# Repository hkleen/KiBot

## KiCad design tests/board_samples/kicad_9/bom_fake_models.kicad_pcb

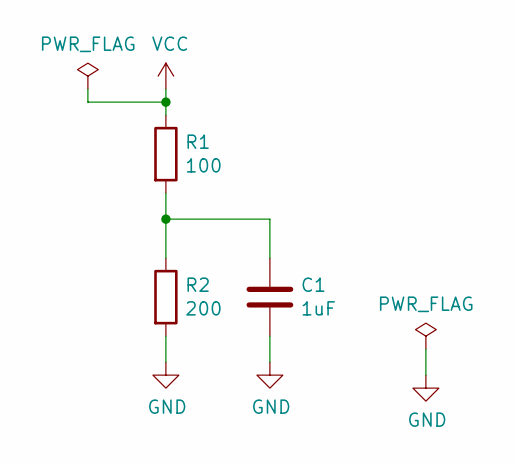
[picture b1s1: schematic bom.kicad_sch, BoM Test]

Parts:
C1: 1uF; C_0805_2012Metric
R1: 100; R_0805_2012Metric
R2: 200; R_0805_2012Metric

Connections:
GND: C1.2, R2.2
unnamed: C1.1, R1.2, R2.1
VCC: R1.1

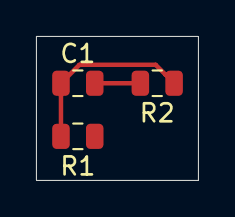
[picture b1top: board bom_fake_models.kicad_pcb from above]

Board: 2 copper layers, 9.0 x 8.0 mm, 3 parts (0 on the bottom side), 2 nets.

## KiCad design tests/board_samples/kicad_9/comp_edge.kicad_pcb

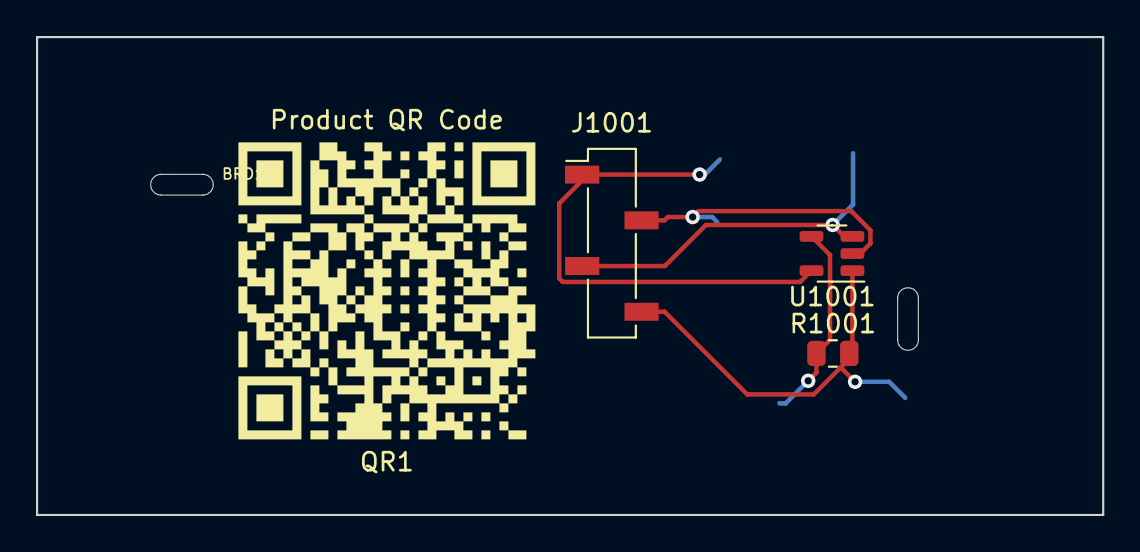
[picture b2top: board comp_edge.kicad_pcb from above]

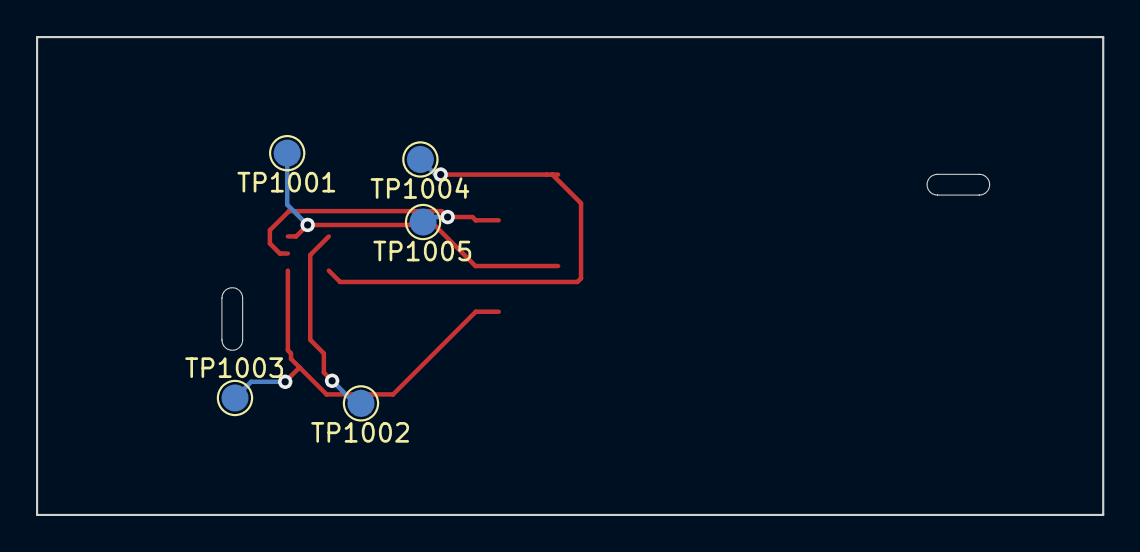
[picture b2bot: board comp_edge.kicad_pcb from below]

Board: 2 copper layers, 59.2 x 26.5 mm, 10 parts (5 on the bottom side), 5 nets.

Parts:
BRD1: SYM_Arrow_XLarge; DemoBoard
J1001: SSM-104-L-SV; PinSocket_1x04_P2.54mm_Vertical_SMD_Pin1Left
QR1: Product QR Code; TC5
R1001: 10k; R_0805_2012Metric
TP1001: TP_IN; TestPoint_Pad_D1.5mm
TP1002: TP_NEG; TestPoint_Pad_D1.5mm
TP1003: TP_OUT; TestPoint_Pad_D1.5mm
TP1004: TP_VCC; TestPoint_Pad_D1.5mm
TP1005: TP_GND; TestPoint_Pad_D1.5mm
U1001: MCP6001-OT; SOT-23-5

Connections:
/IN: J1001.3, TP1001.1, U1001.3
/OUT: J1001.4, R1001.2, TP1003.1, U1001.1
/_AOPIN+: R1001.1, TP1002.1, U1001.4
GND: J1001.2, TP1005.1, U1001.2
VCC: J1001.1, TP1004.1, U1001.5
